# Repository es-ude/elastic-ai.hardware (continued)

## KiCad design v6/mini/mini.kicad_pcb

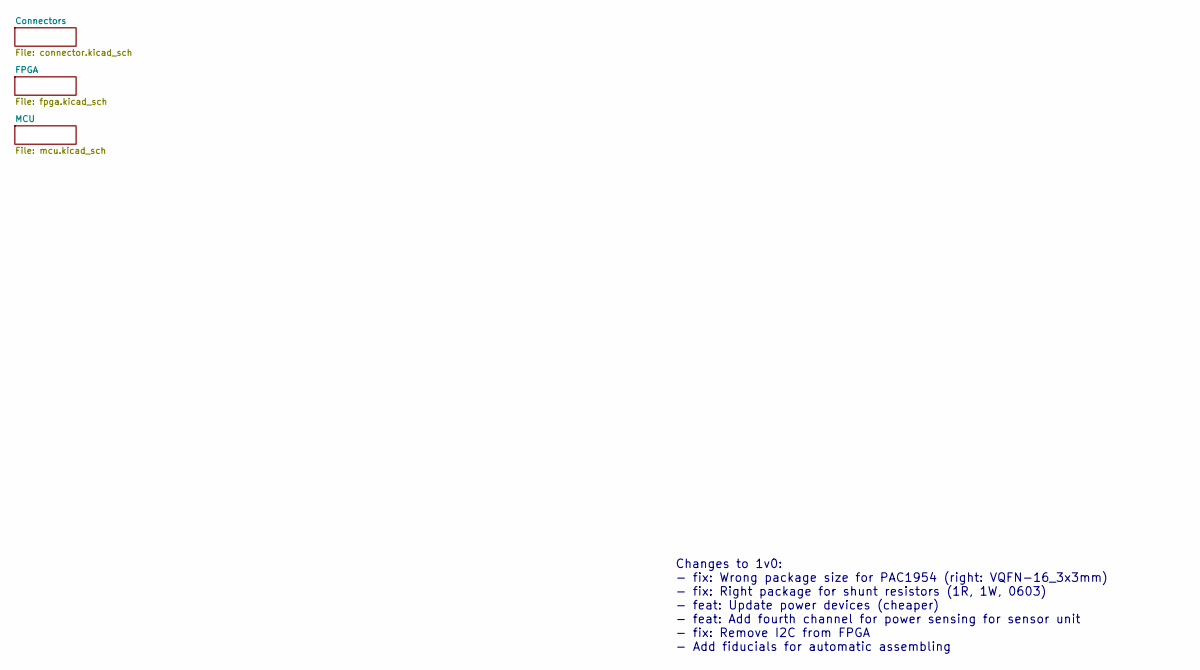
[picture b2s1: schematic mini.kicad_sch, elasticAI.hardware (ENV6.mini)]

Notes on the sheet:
Changes to 1v0: - fix: Wrong package size for PAC1954 (right: VQFN-16_3x3mm) - fix: Right package for shunt resistors (1R, 1W, 0603) - feat: Update power devices (cheaper) - feat: Add fourth channel for power sensing for sensor unit - fix: Remove I2C from FPGA - Add fiducials for automatic assembli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

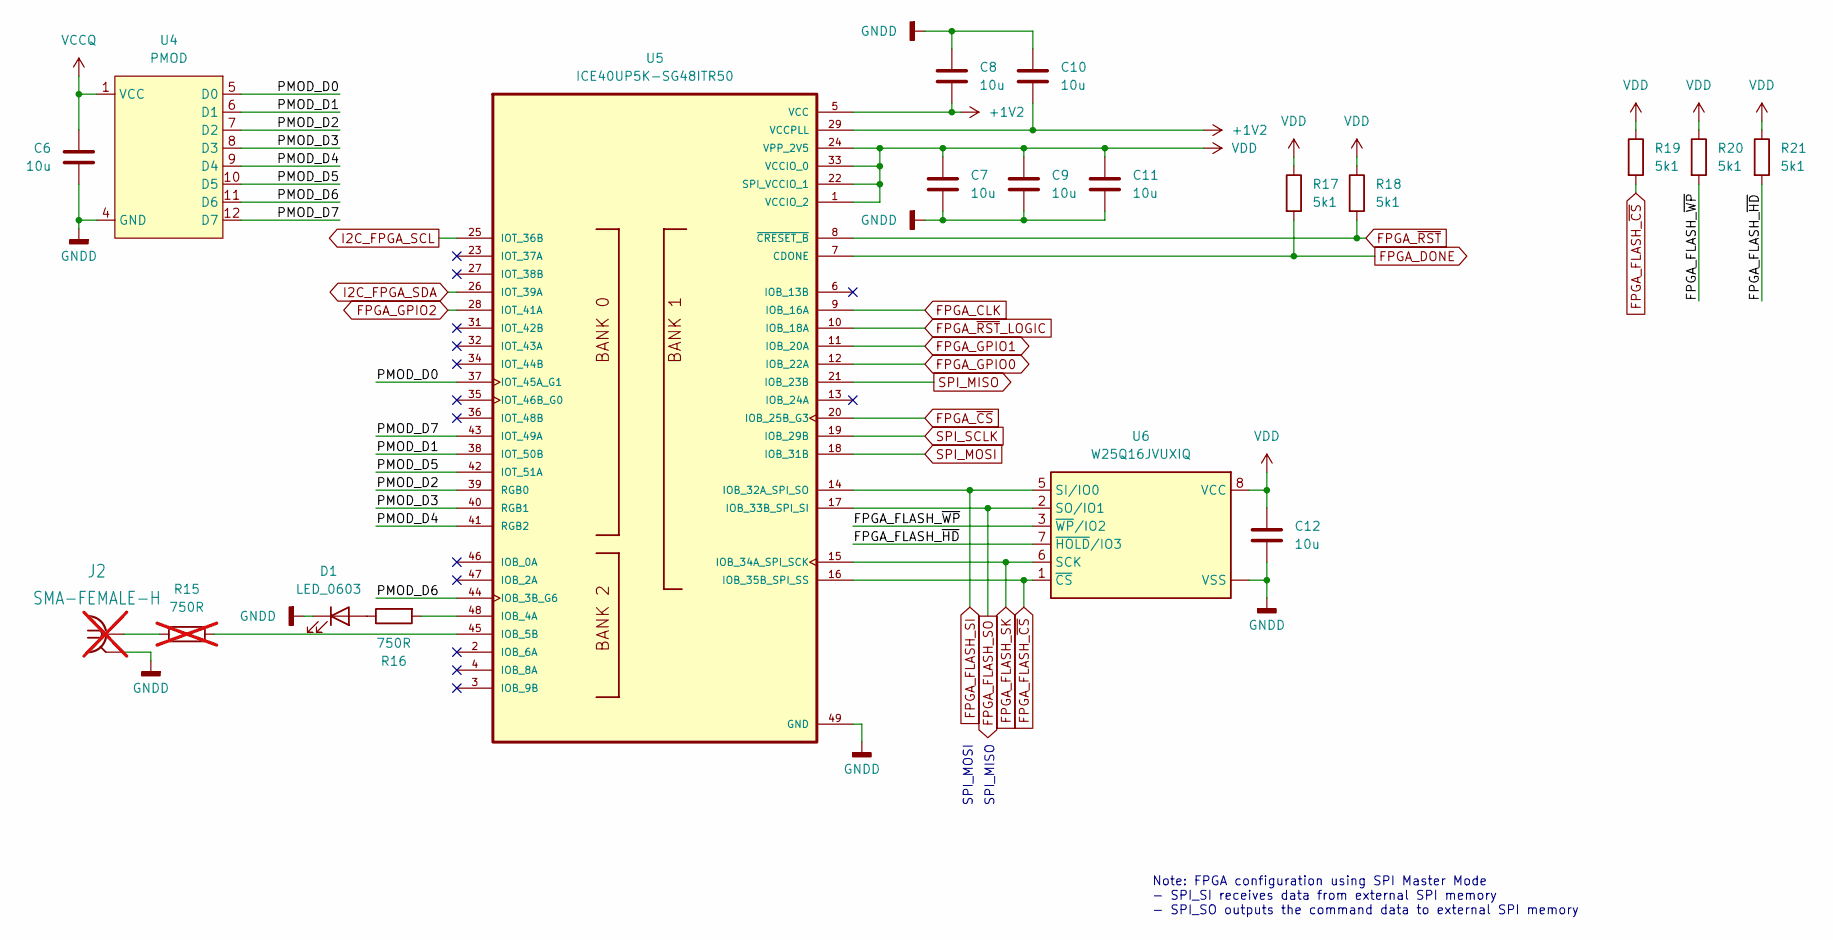
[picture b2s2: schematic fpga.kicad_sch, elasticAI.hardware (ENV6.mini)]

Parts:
C6, C7, C8, C9, C10, C11, C12: 10u; C_0402_1005Metric
D1: LED_0603; LED_0603_1608Metric
J2: SMA-FEMALE-H; SMA_Samtec_SMA-J-P-H-ST-EM1_EdgeMount; not fitted
R15: 750R; R_0402_1005Metric; not fitted
R16: 750R; R_0402_1005Metric
R17, R18, R19, R20, R21: 5k1; R_0402_1005Metric
U4: PMOD; PinSocket_2x06_P2.54mm_Horizontal
U5: ICE40UP5K-SG48ITR50; QFN-48-1EP_7x7mm_P0.5mm_EP5.15x5.15mm; PARTREV 1.4
U6: W25Q16JVUXIQ; USON-8-1EP_3x2mm_P0.5mm_EP0.2x1.6mm

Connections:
+1V2: C8.2, C10.2, U5.5 (VCC), U5.29 (VCCPLL), U5.30 (VCC); also elsewhere on the board
/FPGA/FPGA_FLASH_~HD: R21.2, U6.7 (~HOLD/IO3)
/FPGA/FPGA_FLASH_~WP: R20.2, U6.3 (~WP/IO2)
/FPGA/PMOD_D0: U4.5 (D0), U5.37 (IOT_45A_G1)
/FPGA/PMOD_D1: U4.6 (D1), U5.38 (IOT_50B)
/FPGA/PMOD_D2: U4.7 (D2), U5.39 (RGB0)
/FPGA/PMOD_D3: U4.8 (D3), U5.40 (RGB1)
/FPGA/PMOD_D4: U4.9 (D4), U5.41 (RGB2)
/FPGA/PMOD_D5: U4.10 (D5), U5.42 (IOT_51A)
/FPGA/PMOD_D6: U4.11 (D6), U5.44 (IOB_3B_G6)
/FPGA/PMOD_D7: U4.12 (D7), U5.43 (IOT_49A)
FPGA_CLK: U5.9 (IOB_16A); also elsewhere on the board
FPGA_DONE: R17.2, U5.7 (CDONE); also elsewhere on the board
FPGA_FLASH_SI: U5.14 (IOB_32A_SPI_SO), U6.5 (SI/IO0); also elsewhere on the board
FPGA_FLASH_SK: U5.15 (IOB_34A_SPI_SCK), U6.6 (SCK); also elsewhere on the board
FPGA_FLASH_SO: U5.17 (IOB_33B_SPI_SI), U6.2 (SO/IO1); also elsewhere on the board
FPGA_FLASH_~CS: R19.2, U5.16 (IOB_35B_SPI_SS), U6.1 (~CS); also elsewhere on the board
FPGA_GPIO0: U5.12 (IOB_22A); also elsewhere on the board
FPGA_GPIO1: U5.11 (IOB_20A); also elsewhere on the board
FPGA_GPIO2: U5.28 (IOT_41A); also elsewhere on the board
FPGA_~CS: U5.20 (IOB_25B_G3); also elsewhere on the board
FPGA_~RST: R18.2, U5.8 (~CRESET_B); also elsewhere on the board
FPGA_~RST_LOGIC: U5.10 (IOB_18A); also elsewhere on the board
GNDD: C6.2, C7.2, C8.1, C9.2, C10.1, C11.2, C12.2, D1.1 (K), J2.2 (GND), U4.3 (GND), U4.4 (GND), U5.49 (GND), U6.4 (VSS), U6.9 (VSS); also elsewhere on the board
I2C_FPGA_SCL: U5.25 (IOT_36B); also elsewhere on the board
I2C_FPGA_SDA: U5.26 (IOT_39A); also elsewhere on the board
unnamed: D1.2 (A), R16.1
unnamed: J2.1 (SIG), R15.2
unnamed: R16.2, U5.48 (IOB_4A)
unnamed: R15.1, U5.45 (IOB_5B)
SPI_MISO: U5.21 (IOB_23B); also elsewhere on the board
SPI_MOSI: U5.18 (IOB_31B); also elsewhere on the board
SPI_SCLK: U5.19 (IOB_29B); also elsewhere on the board
VCCQ: C6.1, U4.1 (VCC), U4.2 (VCC); also elsewhere on the board
VDD: C7.1, C9.1, C11.1, C12.1, R17.1, R18.1, R19.1, R20.1, R21.1, U5.1 (VCCIO_2), U5.22 (SPI_VCCIO_1), U5.24 (VPP_2V5), U5.33 (VCCIO_0), U6.8 (VCC); also elsewhere on the board

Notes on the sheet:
SPI_MISO
Note: FPGA configuration using SPI Master Mode - SPI_SI receives data from external SPI memory - SPI_SO outputs the command data to external SPI memory
SPI_MOSI

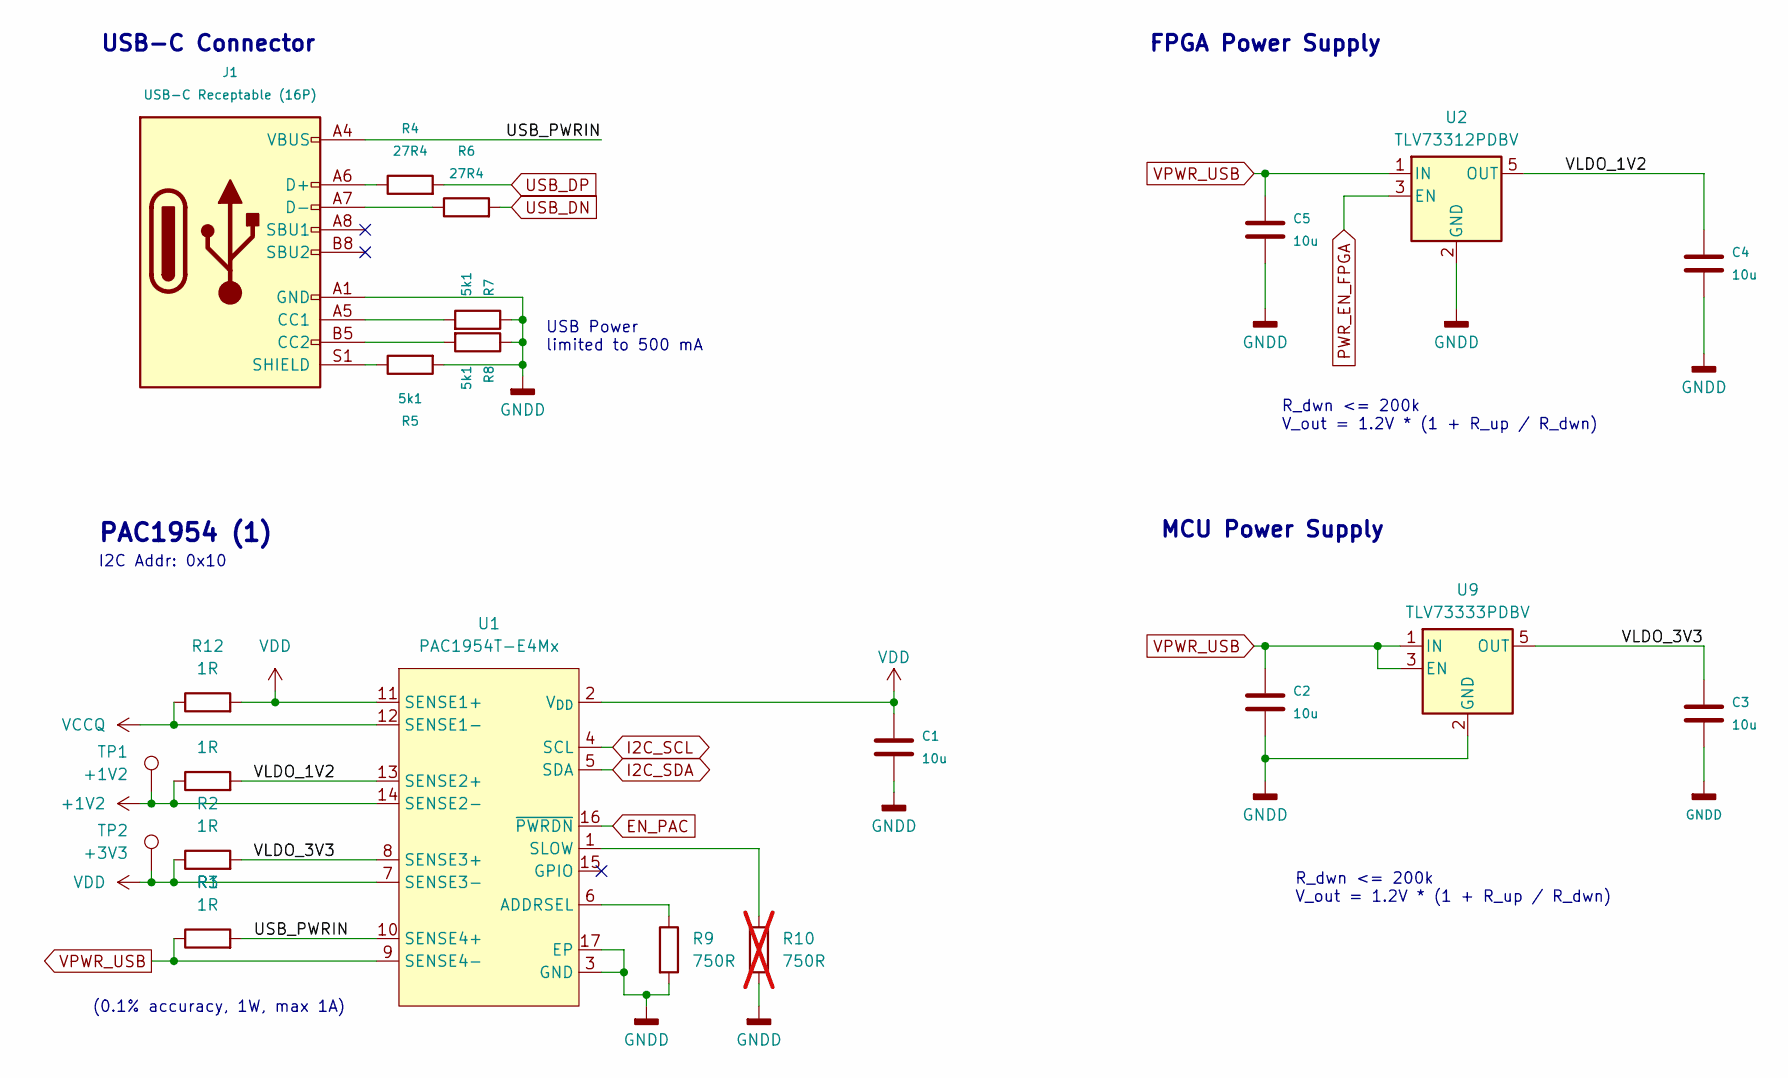
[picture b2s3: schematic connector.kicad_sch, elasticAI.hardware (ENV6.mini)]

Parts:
C1, C2, C3, C4, C5: 10u; C_0402_1005Metric
J1: USB-C Receptable (16P); USB_C_Receptacle_16P
R1, R2, R3, R12: 1R; R_0603_1608Metric
R4, R6: 27R4; R_0402_1005Metric
R5, R7, R8: 5k1; R_0402_1005Metric
R9: 750R; R_0402_1005Metric
R10: 750R; R_0402_1005Metric; not fitted
TP1: +1V2; TestPoint_Pad_D1.0mm
TP2: +3V3; TestPoint_Pad_D1.0mm
U1: PAC1954T-E4Mx; VQFN-16-1EP_3x3mm_P0.5mm_EP1.1x1.1mm
U2: TLV73312PDBV; SOT-23-5
U9: TLV73333PDBV; SOT-23-5

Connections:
+1V2: R1.1, TP1.1 (1_1), U1.14 (SENSE2-); also elsewhere on the board
/Connectors/USB_PWRIN: J1.A4 (VBUS), J1.A9 (VBUS), J1.B4 (VBUS), J1.B9 (VBUS), R3.2, U1.10 (SENSE4+)
/Connectors/VLDO_1V2: C4.2, R1.2, U1.13 (SENSE2+), U2.5 (OUT)
/Connectors/VLDO_3V3: C3.2, R2.2, U1.8 (SENSE3+), U9.5 (OUT)
EN_PAC: U1.16 (~PWRDN); also elsewhere on the board
GNDD: C1.1, C2.1, C3.1, C4.1, C5.1, J1.A1 (GND), J1.A12 (GND), J1.B1 (GND), J1.B12 (GND), R5.2, R7.1, R8.1, R9.2, R10.2, U1.3 (GND), U1.17 (EP), U2.2 (GND), U9.2 (GND); also elsewhere on the board
I2C_SCL: U1.4 (SCL); also elsewhere on the board
I2C_SDA: U1.5 (SDA); also elsewhere on the board
unnamed: J1.A5 (CC1), R7.2
unnamed: J1.B5 (CC2), R8.2
unnamed: J1.A6 (D+), J1.B6 (D+), R4.1
unnamed: J1.A7 (D-), J1.B7 (D-), R6.1
unnamed: J1.S1 (SHIELD), R5.1
unnamed: R9.1, U1.6 (ADDRSEL)
unnamed: R10.1, U1.1 (SLOW)
PWR_EN_FPGA: U2.3 (EN); also elsewhere on the board
USB_DN: R6.2; also elsewhere on the board
USB_DP: R4.2; also elsewhere on the board
VCCQ: R12.1, U1.12 (SENSE1-); also elsewhere on the board
VDD: C1.2, R2.1, R12.2, TP2.1 (1_1), U1.2 (V_{DD}), U1.7 (SENSE3-), U1.11 (SENSE1+); also elsewhere on the board
VPWR_USB: C2.2, C5.2, R3.1, U1.9 (SENSE4-), U2.1 (IN), U9.1 (IN), U9.3 (EN)

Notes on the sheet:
R_dwn <= 200k V_out = 1.2V * (1 + R_up / R_dwn)
FPGA Power Supply
I2C Addr: 0x10
PAC1954 (1)
USB-C Connector
(0.1% accuracy, 1W, max 1A)
USB Power limited to 500 mA
MCU Power Supply

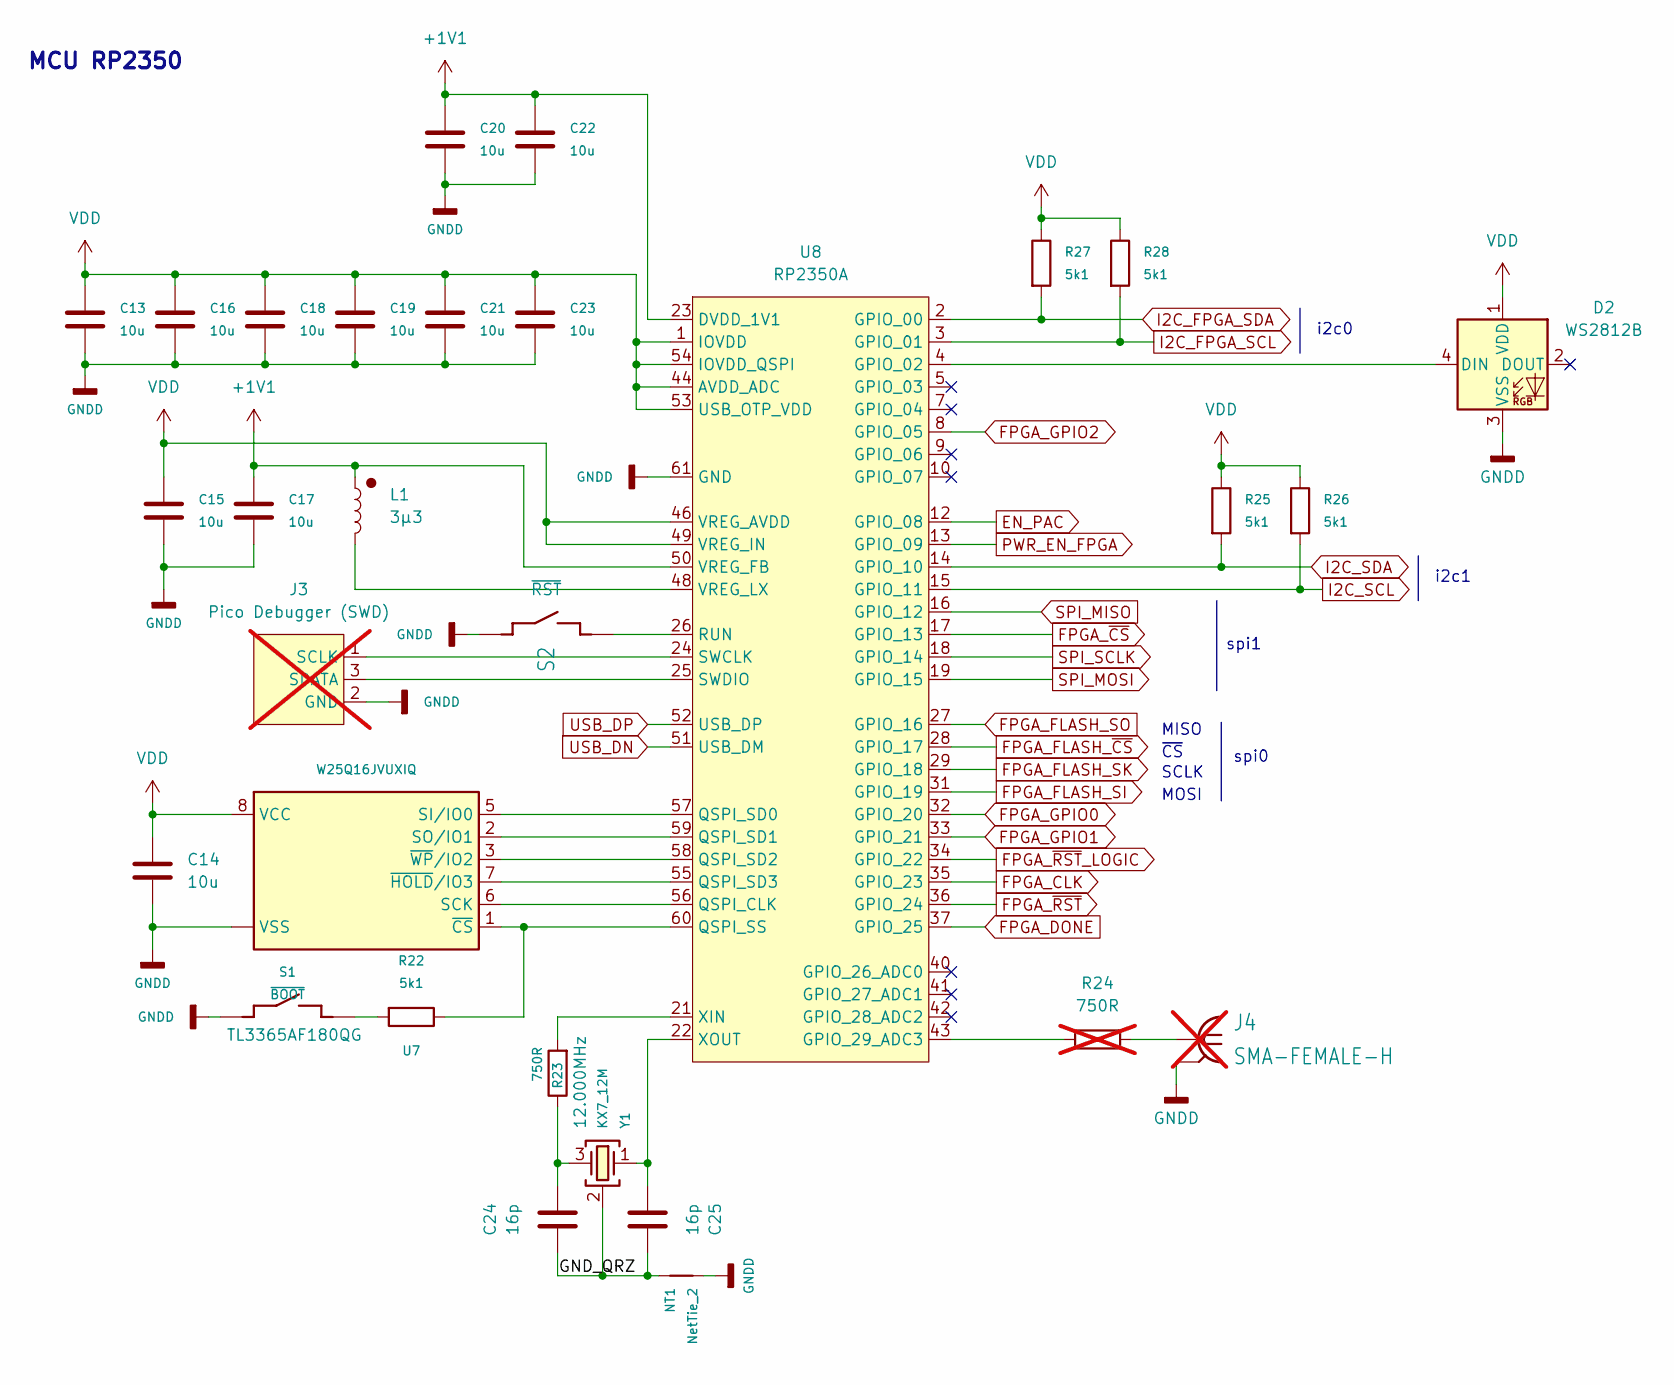
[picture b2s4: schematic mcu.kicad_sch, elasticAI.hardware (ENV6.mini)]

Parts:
C13, C14, C15, C16, C17, C18, C19, C20, C21, C22, C23: 10u; C_0402_1005Metric
C24, C25: 16p; C_0402_1005Metric
D2: WS2812B; LED_WS2812B_PLCC4_5.0x5.0mm_P3.2mm
J3: Pico Debugger (SWD); PinHeader_1x03_P2.54mm_Vertical; not fitted
J4: SMA-FEMALE-H; SMA_Samtec_SMA-J-P-H-ST-EM1_EdgeMount; not fitted
L1: 3µ3; L_0805_2012_metric_Alligned_HandSolder
NT1: NetTie_2; NetTie-2_SMD_Pad0.5mm
R22, R25, R26, R27, R28: 5k1; R_0402_1005Metric
R23: 750R; R_0402_1005Metric
R24: 750R; R_0402_1005Metric; not fitted
S1: ~{BOOT}; TACTILE-SWITCH
S2: ~{RST}; TACTILE-SWITCH
U7: W25Q16JVUXIQ; USON-8-1EP_3x2mm_P0.5mm_EP0.2x1.6mm
U8: RP2350A; QFN-60_EP_7x7_Pitch0.4mm
Y1: KX7_12M; KX-7; MPN ABM8G-25.000MHZ-18-D2Y-T3

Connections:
+1V1: C17.2, C20.2, C22.2, L1.1, U8.6 (DVDD_1V1), U8.23 (DVDD_1V1), U8.39 (DVDD_1V1), U8.50 (VREG_FB)
/MCU/GND_QRZ: C24.1, C25.1, NT1.2, Y1.2 (SH), Y1.4 (SH)
EN_PAC: U8.12 (GPIO_08); also elsewhere on the board
FPGA_CLK: U8.35 (GPIO_23); also elsewhere on the board
FPGA_DONE: U8.37 (GPIO_25); also elsewhere on the board
FPGA_FLASH_SI: U8.31 (GPIO_19); also elsewhere on the board
FPGA_FLASH_SK: U8.29 (GPIO_18); also elsewhere on the board
FPGA_FLASH_SO: U8.27 (GPIO_16); also elsewhere on the board
FPGA_FLASH_~CS: U8.28 (GPIO_17); also elsewhere on the board
FPGA_GPIO0: U8.32 (GPIO_20); also elsewhere on the board
FPGA_GPIO1: U8.33 (GPIO_21); also elsewhere on the board
FPGA_GPIO2: U8.8 (GPIO_05); also elsewhere on the board
FPGA_~CS: U8.17 (GPIO_13); also elsewhere on the board
FPGA_~RST: U8.36 (GPIO_24); also elsewhere on the board
FPGA_~RST_LOGIC: U8.34 (GPIO_22); also elsewhere on the board
GNDD: C13.1, C14.2, C15.1, C16.1, C17.1, C18.1, C19.1, C20.1, C21.1, C22.1, C23.1, D2.3 (VSS), J3.2 (GND), J4.2 (GND), NT1.1, S1.1, S1.2 (1), S2.1, S2.2 (1), U7.4 (VSS), U7.9 (VSS), U8.47 (GND), U8.61 (GND); also elsewhere on the board
I2C_FPGA_SCL: R28.2, U8.3 (GPIO_01); also elsewhere on the board
I2C_FPGA_SDA: R27.2, U8.2 (GPIO_00); also elsewhere on the board
I2C_SCL: R26.2, U8.15 (GPIO_11); also elsewhere on the board
I2C_SDA: R25.2, U8.14 (GPIO_10); also elsewhere on the board
unnamed: C24.2, R23.1, Y1.3
unnamed: D2.4 (DIN), U8.4 (GPIO_02)
unnamed: J3.1 (SCLK), U8.24 (SWCLK)
unnamed: J3.3 (SDATA), U8.25 (SWDIO)
unnamed: J4.1 (SIG), R24.2
unnamed: R22.2, S1.3 (2), S1.4 (2)
unnamed: U7.6 (SCK), U8.56 (QSPI_CLK)
unnamed: U7.5 (SI/IO0), U8.57 (QSPI_SD0)
unnamed: U7.2 (SO/IO1), U8.59 (QSPI_SD1)
unnamed: R22.1, U7.1 (~CS), U8.60 (QSPI_SS)
unnamed: U7.7 (~HOLD/IO3), U8.55 (QSPI_SD3)
unnamed: U7.3 (~WP/IO2), U8.58 (QSPI_SD2)
unnamed: R24.1, U8.43 (GPIO_29_ADC3)
unnamed: S2.3 (2), S2.4 (2), U8.26 (RUN)
unnamed: L1.2, U8.48 (VREG_LX)
unnamed: R23.2, U8.21 (XIN)
unnamed: C25.2, U8.22 (XOUT), Y1.1
PWR_EN_FPGA: U8.13 (GPIO_09); also elsewhere on the board
SPI_MISO: U8.16 (GPIO_12); also elsewhere on the board
SPI_MOSI: U8.19 (GPIO_15); also elsewhere on the board
SPI_SCLK: U8.18 (GPIO_14); also elsewhere on the board
USB_DN: U8.51 (USB_DM); also elsewhere on the board
USB_DP: U8.52 (USB_DP); also elsewhere on the board
VDD: C13.2, C14.1, C15.2, C16.2, C18.2, C19.2, C21.2, C23.2, D2.1 (VDD), R25.1, R26.1, R27.1, R28.1, U7.8 (VCC), U8.1 (IOVDD), U8.11 (IOVDD), U8.20 (IOVDD), U8.30 (IOVDD), U8.38 (IOVDD), U8.44 (AVDD_ADC), U8.45 (IOVDD), U8.46 (VREG_AVDD), U8.49 (VREG_IN), U8.53 (USB_OTP_VDD), U8.54 (IOVDD_QSPI); also elsewhere on the board

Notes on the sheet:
i2c0
~{CS}
SCLK
MISO
i2c1
MCU RP2350
MOSI
spi0
spi1

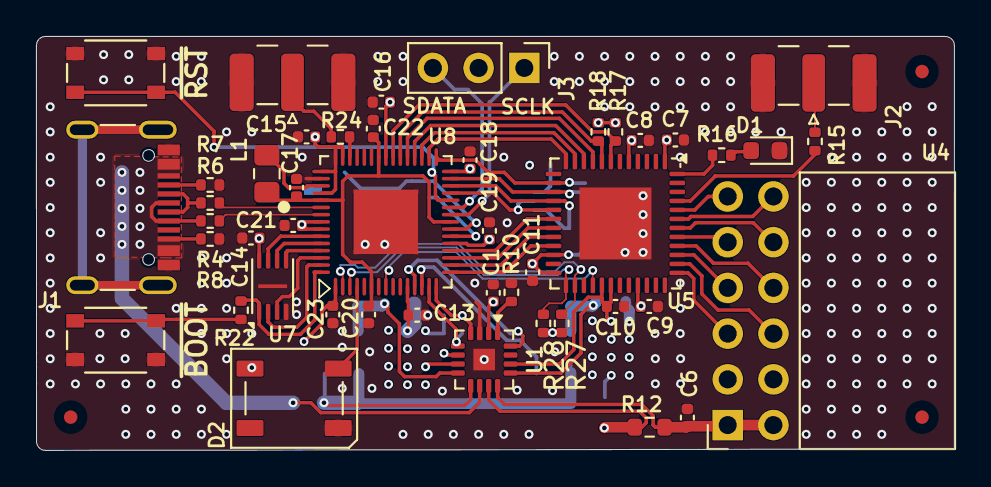
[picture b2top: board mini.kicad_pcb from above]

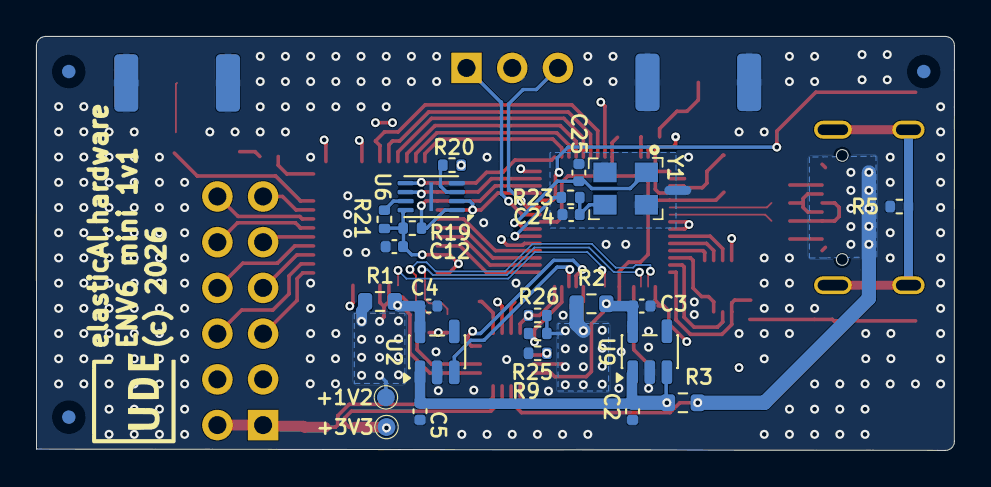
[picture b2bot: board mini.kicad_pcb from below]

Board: 4 copper layers, 51.0 x 23.0 mm, 71 parts (25 on the bottom side), 71 nets.

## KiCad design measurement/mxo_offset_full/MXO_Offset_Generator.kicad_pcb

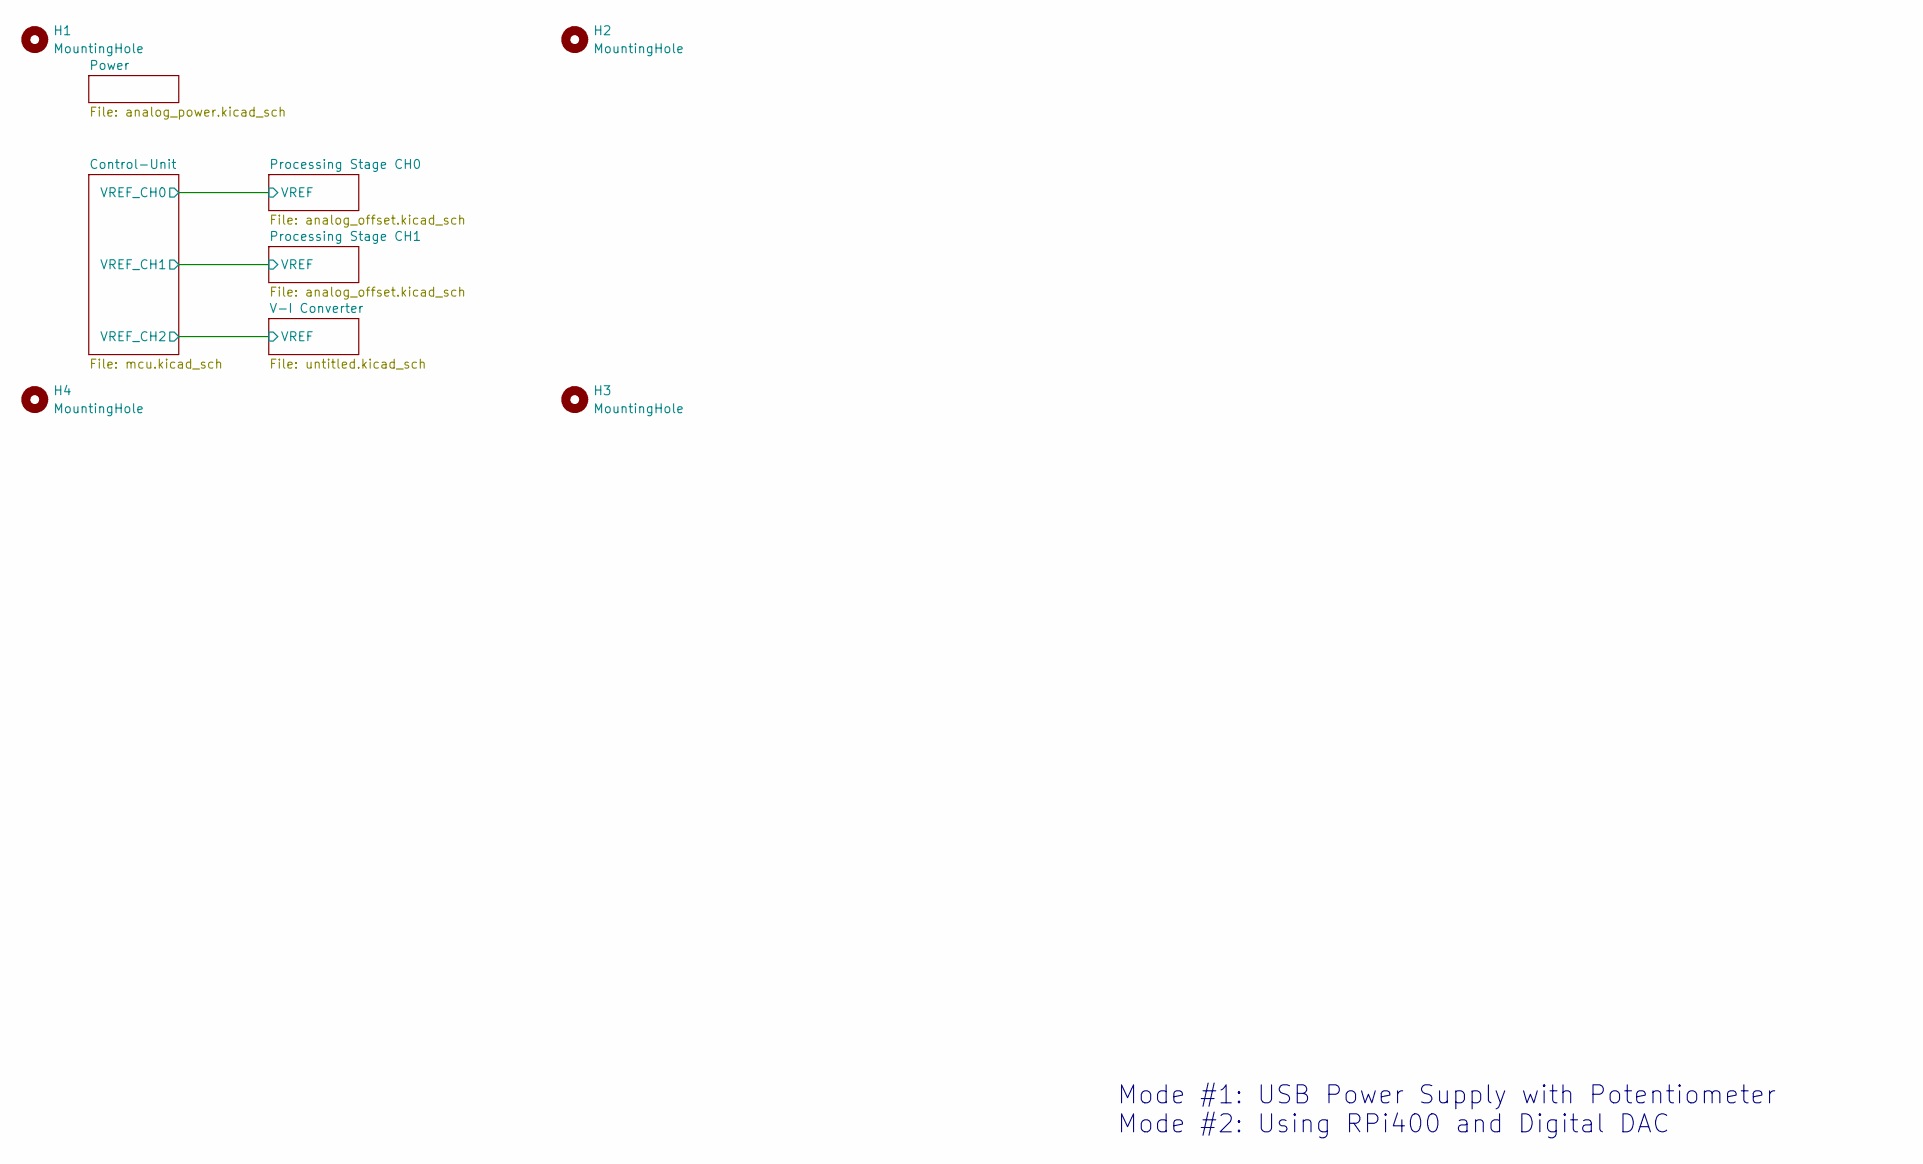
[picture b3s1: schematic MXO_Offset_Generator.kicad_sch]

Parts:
H1, H2, H3, H4: MountingHole; MountingHole_3.2mm_M3

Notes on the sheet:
Mode #1: USB Power Supply with Potentiometer Mode #2: Using RPi400 and Digital DAC

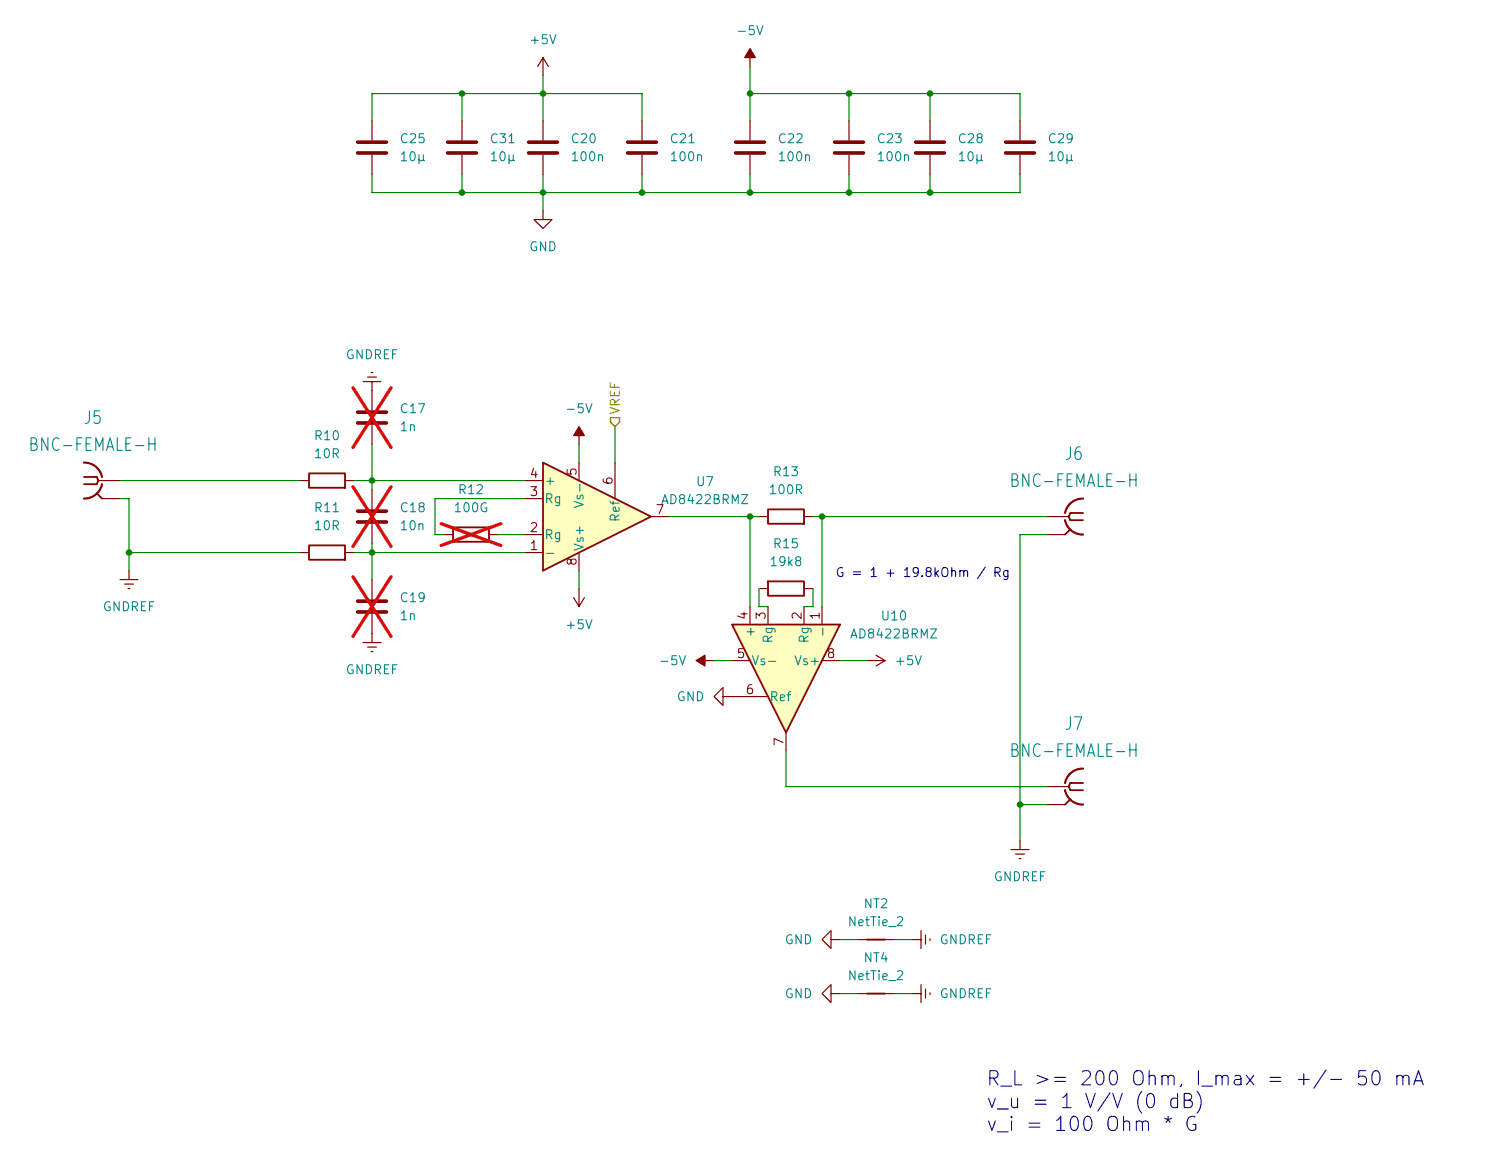
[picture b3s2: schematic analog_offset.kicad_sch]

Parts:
C17, C19: 1n; C_0402_1005Metric; not fitted
C18: 10n; C_0402_1005Metric; not fitted
C20, C21, C22, C23: 100n; C_0402_1005Metric
C25, C28, C29, C31: 10µ; C_0805_2012Metric
J5, J6, J7: BNC-FEMALE-H; BNC-MALE-H
NT2, NT4: NetTie_2; NetTie-2_SMD_Pad0.5mm
R10, R11: 10R; R_0402_1005Metric
R12: 100G; R_0402_1005Metric; not fitted
R13: 100R; R_0402_1005Metric
R15: 19k8; R_0402_1005Metric
U7, U10: AD8422BRMZ; MSOP-8_3x3mm_P0.65mm

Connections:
+5V: C20.1, C21.1, C25.1, C31.1, U7.8 (Vs+), U10.8 (Vs+); also elsewhere on the board
-5V: C22.1, C23.1, C28.1, C29.1, U7.5 (Vs-), U10.5 (Vs-); also elsewhere on the board
/Control-Unit/VREF_CH1: U7.6 (Ref); also elsewhere on the board
GND: C20.2, C21.2, C22.2, C23.2, C25.2, C28.2, C29.2, C31.2, NT2.1, NT4.1, U10.6 (Ref); also elsewhere on the board
GNDREF: C17.1, C19.2, J5.2 (GND), J6.2 (GND), J7.2 (GND), NT2.2, NT4.2, R11.1; also elsewhere on the board
unnamed: J5.1 (SIG), R10.1
unnamed: J6.1 (SIG), R13.2, U10.1 (-)
unnamed: J7.1 (SIG), U10.7
unnamed: R12.1, U7.2 (Rg)
unnamed: R12.2, U7.3 (Rg)
unnamed: R15.1, U10.2 (Rg)
unnamed: R15.2, U10.3 (Rg)
unnamed: C17.2, C18.1, R10.2, U7.4 (+)
unnamed: C18.2, C19.1, R11.2, U7.1 (-)
unnamed: R13.1, U7.7, U10.4 (+)

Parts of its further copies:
C10, C12: 1n; C_0402_1005Metric; not fitted
C11: 10n; C_0402_1005Metric; not fitted
C13, C14, C15, C16: 100n; C_0402_1005Metric
C24, C26, C27, C30: 10µ; C_0805_2012Metric
J2, J3, J4: BNC-FEMALE-H; BNC-MALE-H
NT1, NT5: NetTie_2; NetTie-2_SMD_Pad0.5mm
R6, R7: 10R; R_0402_1005Metric
R8: 100G; R_0402_1005Metric; not fitted
R9: 100R; R_0402_1005Metric
R14: 19k8; R_0402_1005Metric
U6, U9: AD8422BRMZ; MSOP-8_3x3mm_P0.65mm

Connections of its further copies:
+5V: C13.1, C14.1, C24.1, C30.1, U6.8 (Vs+), U9.8 (Vs+); also elsewhere on the board
-5V: C15.1, C16.1, C26.1, C27.1, U6.5 (Vs-), U9.5 (Vs-); also elsewhere on the board
/Control-Unit/VREF_CH0: U6.6 (Ref); also elsewhere on the board
GND: C13.2, C14.2, C15.2, C16.2, C24.2, C26.2, C27.2, C30.2, NT1.1, NT5.1, U9.6 (Ref); also elsewhere on the board
GNDREF: C10.1, C12.2, J2.2 (GND), J3.2 (GND), J4.2 (GND), NT1.2, NT5.2, R7.1; also elsewhere on the board
unnamed: J2.1 (SIG), R6.1
unnamed: J3.1 (SIG), R9.2, U9.1 (-)
unnamed: J4.1 (SIG), U9.7
unnamed: R8.1, U6.2 (Rg)
unnamed: R8.2, U6.3 (Rg)
unnamed: R14.1, U9.2 (Rg)
unnamed: R14.2, U9.3 (Rg)
unnamed: C10.2, C11.1, R6.2, U6.4 (+)
unnamed: C11.2, C12.1, R7.2, U6.1 (-)
unnamed: R9.1, U6.7, U9.4 (+)

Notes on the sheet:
R_L >= 200 Ohm, I_max = +/- 50 mA v_u = 1 V/V (0 dB) v_i = 100 Ohm * G
G = 1 + 19.8kOhm / Rg

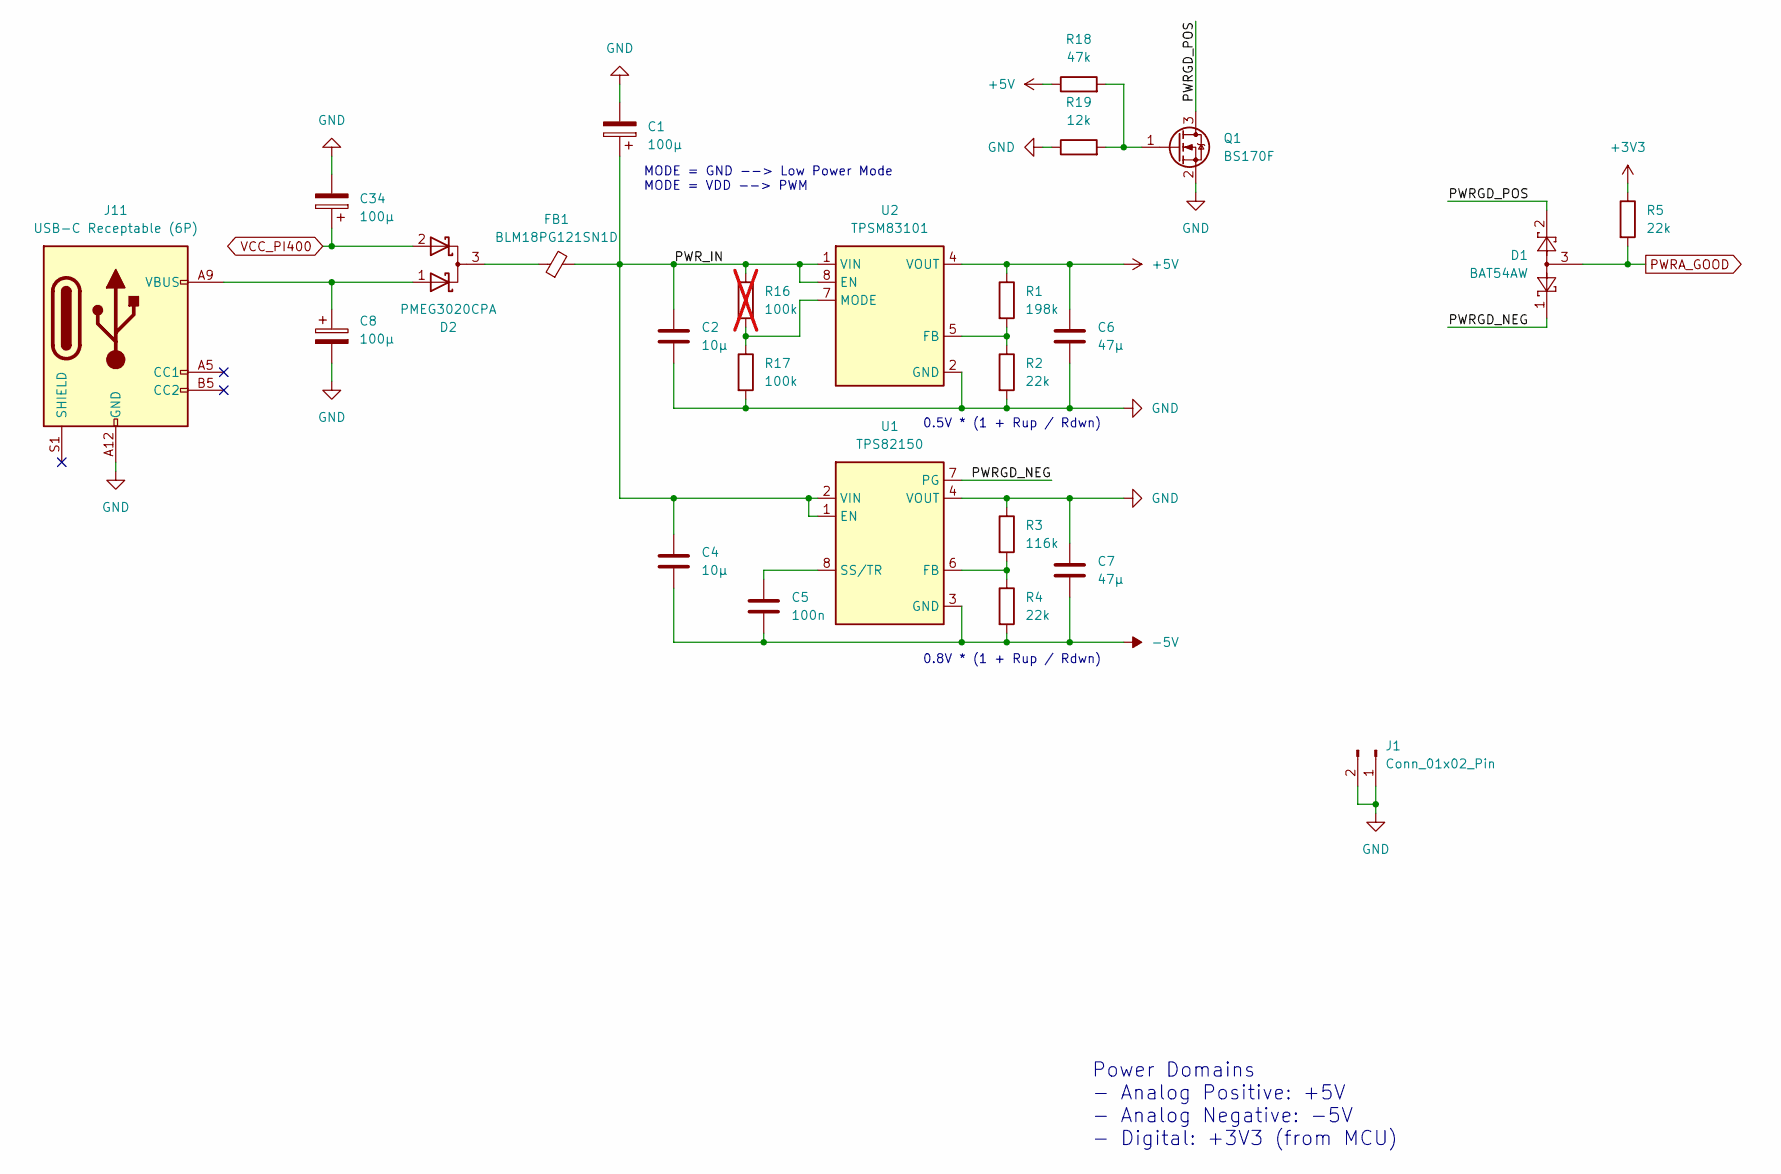
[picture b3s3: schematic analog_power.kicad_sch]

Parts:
C1, C8, C34: 100µ; CP_Elec_4x3
C2, C4: 10µ; C_0805_2012Metric
C5: 100n; C_0402_1005Metric
C6, C7: 47µ; C_1206_3216Metric
D1: BAT54AW; SOT-323_SC-70
D2: PMEG3020CPA; HUSON-3-1EP_2x2mm_P1.3mm_EP1.1x1.6mm
FB1: FB_120Z_2A_0603; L_0603_1608Metric; MPN BLM18PG121SN1D
J1: Conn_01x02_Pin; PinHeader_1x02_P2.54mm_Vertical
J11: USB-C Receptable (6P); USB_C_Receptacle_6P
Q1: BS170F; SOT-23
R1: 198k; R_0402_1005Metric
R2, R4, R5: 22k; R_0402_1005Metric
R3: 116k; R_0402_1005Metric
R16: 100k; R_0402_1005Metric; not fitted
R17: 100k; R_0402_1005Metric
R18: 47k; R_0402_1005Metric
R19: 12k; R_0402_1005Metric
U1: TPS82150; Texas_SIL0008D_MicroSiP-8-1EP_2.8x3mm_P0.65mm_EP1.1x1.9mm
U2: TPSM83101; MICROSIP8_SIU_TEX

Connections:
+3V3: R5.1; also elsewhere on the board
+5V: C6.1, R1.1, R18.1, U2.4 (VOUT); also elsewhere on the board
-5V: C4.2, C5.2, C7.2, R4.2, U1.3 (GND), U1.9 (GND); also elsewhere on the board
/Power/PWRGD_NEG: D1.1, U1.7 (PG)
/Power/PWRGD_POS: D1.2, Q1.3 (D)
/Power/PWR_IN: C1.1, C2.1, C4.1, FB1.2, R16.1, U1.1 (EN), U1.2 (VIN), U2.1 (VIN), U2.8 (EN)
GND: C1.2, C2.2, C6.2, C7.1, C8.2, C34.2, J1.1, J1.2, J11.A12 (GND), J11.B12 (GND), Q1.2 (S), R2.2, R3.1, R17.2, R19.1, U1.4 (VOUT), U1.5 (VOUT), U2.2 (GND), U2.3 (GND), U2.6 (GND); also elsewhere on the board
unnamed: C8.1, D2.1 (K), J11.A9 (VBUS), J11.B9 (VBUS)
unnamed: D2.3 (A), FB1.1
unnamed: Q1.1 (G), R18.2, R19.2
unnamed: R3.2, R4.1, U1.6 (FB)
unnamed: C5.1, U1.8 (SS/TR)
unnamed: R1.2, R2.1, U2.5 (FB)
unnamed: R16.2, R17.1, U2.7 (MODE)
PWRA_GOOD: D1.3, R5.2; also elsewhere on the board
VCC_PI400: C34.1, D2.2 (K); also elsewhere on the board

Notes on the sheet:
0.5V * (1 + Rup / Rdwn)
0.8V * (1 + Rup / Rdwn)
Power Domains - Analog Positive: +5V - Analog Negative: -5V - Digital: +3V3 (from MCU)
MODE = GND --> Low Power Mode MODE = VDD --> PWM
